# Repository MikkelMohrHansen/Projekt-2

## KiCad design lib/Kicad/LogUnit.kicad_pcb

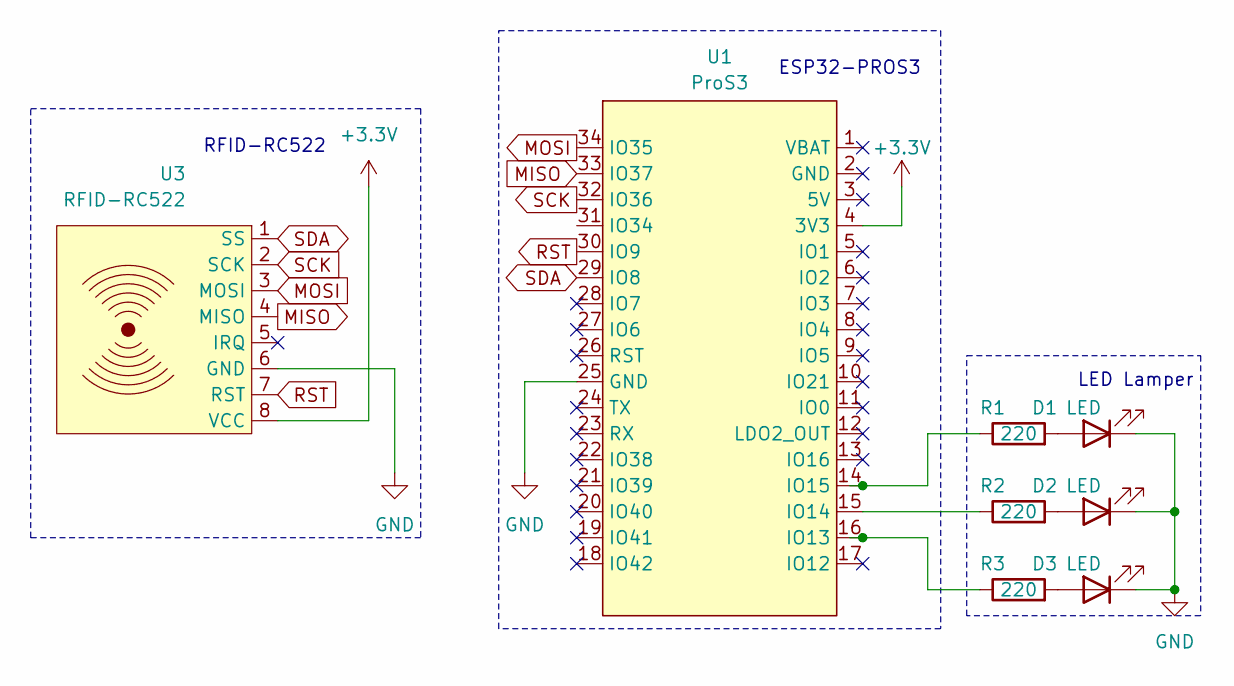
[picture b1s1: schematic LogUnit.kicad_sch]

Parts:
D1, D2, D3: LED; LED_0603_1608Metric_Pad1.05x0.95mm_HandSolder
R1, R2, R3: 220; R_0402_1005Metric_Pad0.72x0.64mm_HandSolder
U1: ProS3; ESP32-PROS3
U3: RFID-RC522; PinHeader_1x08_P2.54mm_Vertical

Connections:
+3.3V: U1.4 (3V3), U3.8 (VCC); also elsewhere on the board
GND: D1.1 (K), D2.1 (K), D3.1 (K), U1.25 (GND), U3.6 (GND); also elsewhere on the board
MISO: U1.33 (IO37), U3.4 (MISO)
MOSI: U1.34 (IO35), U3.3 (MOSI)
unnamed: D1.2 (A), R1.2
unnamed: D2.2 (A), R2.2
unnamed: D3.2 (A), R3.2
unnamed: R3.1, U1.16 (IO13)
unnamed: R2.1, U1.15 (IO14)
unnamed: R1.1, U1.14 (IO15)
RST: U1.30 (IO9), U3.7 (RST)
SCK: U1.32 (IO36), U3.2 (SCK)
SDA: U1.29 (IO8), U3.1 (SS)

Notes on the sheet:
RFID-RC522
LED Lamper
ESP32-PROS3

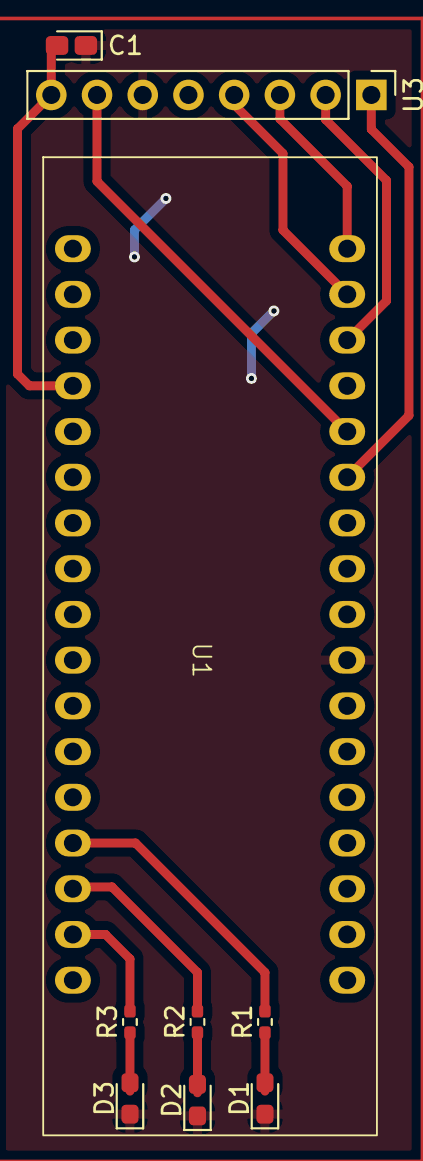
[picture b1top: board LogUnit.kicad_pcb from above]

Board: 2 copper layers, 9 parts (0 on the bottom side), 13 nets.

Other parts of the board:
C1: C; CP_EIA-1608-08_AVX-J_Pad1.25x1.05mm_HandSolder

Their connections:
+3.3V: C1.2; also elsewhere on the board
GND: C1.1; also elsewhere on the board

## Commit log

2024-04-30 DB with dockerfile
2024-05-01 db virker
2024-05-01 Initial Structure, room generation, basic MySQL layout
2024-05-01 Added port
2024-05-02 DBSimpel test program
2024-05-06 added connection that works
2024-05-07 added volumes
2024-05-07 login html and js
2024-05-07 Basic dashboard, nginx.conf
2024-05-07 Login Script, Ændring på mappestruktur. Dashboard hjemmeside prototype. Omnavngiving af 'web' mappen.
2024-05-09 backend-api demo
2024-05-09 Backend, nginx.conf
2024-05-09 schematics
2024-05-09 Nginx configuration
2024-05-09 nginx dockerfile
2024-05-09 PCB done
2024-05-09 Kryptografi test
2024-05-13 clean up
2024-05-14 LogunitDB
2024-05-14 updateret DB
2024-05-14 Send & Receive encrypted data
    Virker. aes1.py skal koges sammen med MFRC522 på ESP siden, recvcrypt.py skal koges sammen med backend.py
2024-05-15 Updated driver and esp script
2024-05-15 Driver og reader til Logunit
    Virker fint til at læse med
2024-05-15 updated kicad
2024-05-20 Updated dockercompose
2024-05-20 Search prototype, css updated, updated driver/esp code
2024-05-22 Prototyping
2024-05-22 Added profile functionality
2024-05-22 Fixed profile function
2024-05-22 Oprydning
2024-05-23 Delete db/navn_connector.py
    pw og username til MySQL... 8)
2024-05-26 Update LogUnit
    Sender Student ID (data på kortet) og Room ID
2024-05-27 bcrypt implementering
2024-05-27 Added: Create new user option on login screen.
2024-05-27 Update check in
2024-05-28 dockerfile 5.0
2024-05-28 updateret til korrekt password
2024-05-28 ændrede port
2024-05-28 Added: List team page
2024-05-28 Update
    Giver succesfuldt check-in
2024-05-28 Blink update
    Gul lampe kommer senere
2024-05-29 cleanup and updated db
2024-05-29 Added: Create new student feature and retrieve list of created students on webpage.
2024-05-29 Added: Search function when creating student, delete student feature implemented, cleaned up backend script, fixed typo.
2024-05-29 Fixed typo's
2024-05-29 cleanup program
2024-05-30 added slutdato
2024-05-30 Added: Write program for RFID cards (Wifi / student card), Wifi connection with RFID card added, student check in graph on student individual profile
2024-05-30 Typo
2024-05-30 Fixed typo
2024-05-30 Fixed Graph
2024-05-30 small change
2024-05-31 LogUnit 3D models
    LogUnit housing and backplate 3D models.
2024-05-31 Updated Graph, added images to website
2024-05-31 added AttendTableClass
2024-05-31 added attendtable
2024-05-31 Added student average javascript on website and real time check in status on student page
2024-05-31 Moved temp folder
2024-06-03 added timestamp
2024-06-03 Added logo to website
2024-06-03 Cleaned up temp folder
2024-06-03 added to attendtable
2024-06-03 Added student check in timestamp
2024-06-03 Make it so that it only makes on query call
2024-06-03 Added reconnect function to MySQL
2024-06-03 Clean up redudant code
2024-06-03 Fixed get student table issues
2024-06-04 Added create room, retrieve rooms list and delete room function to website
2024-06-04 Removed graph and fixed typos in list rooms
2024-06-04 updated nginx dockerfile
2024-06-05 Cleaned up attendance_percentage to a 2 decimal float
2024-06-05 Added student enddate inputbox when creating new student
2024-06-05 Update student.html
    slåfejl
2024-06-05 Slåfejl
2024-06-11 Update mfrc522
